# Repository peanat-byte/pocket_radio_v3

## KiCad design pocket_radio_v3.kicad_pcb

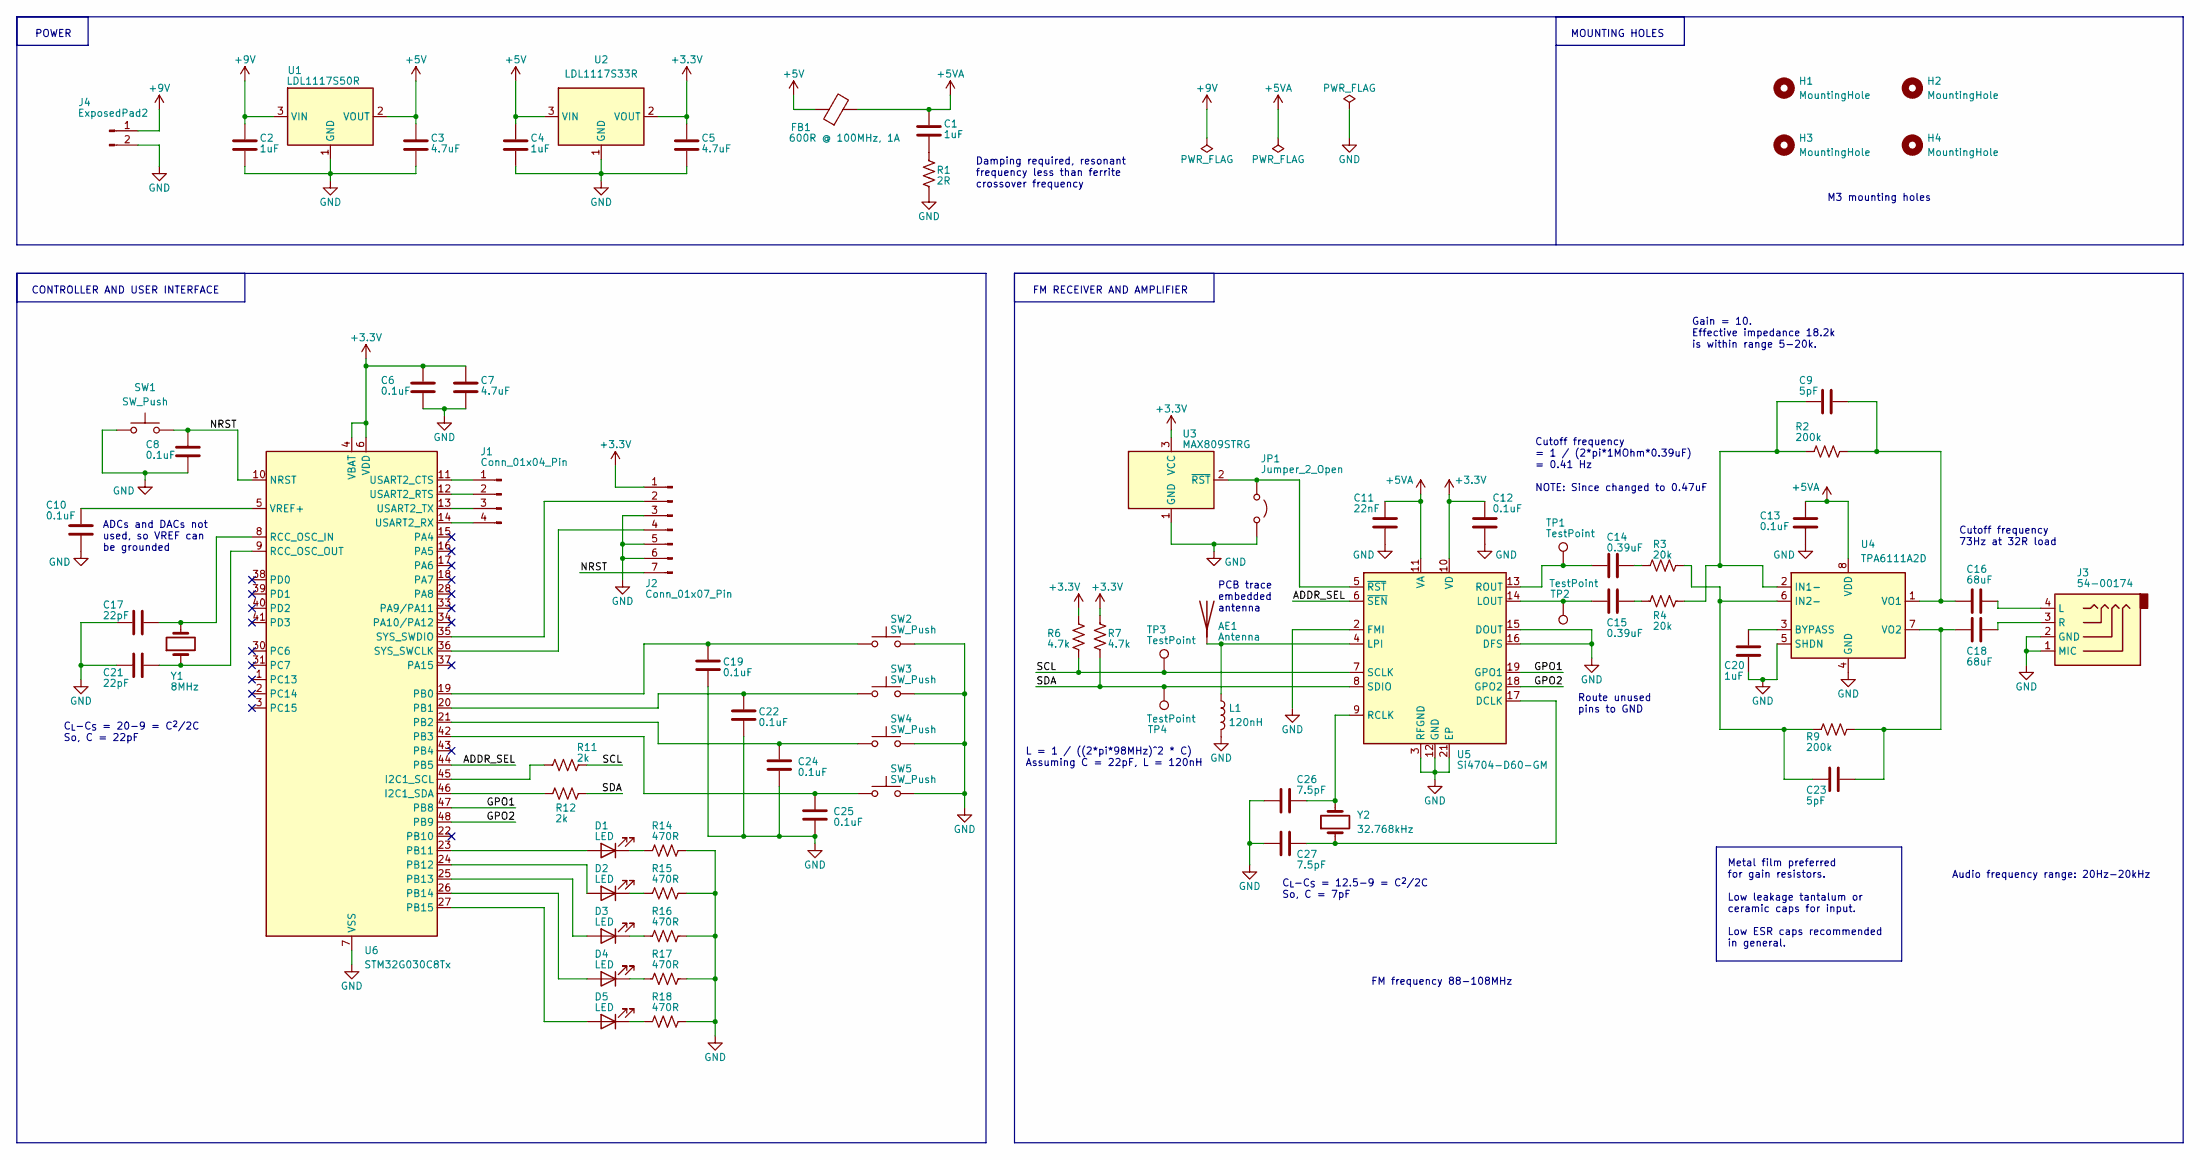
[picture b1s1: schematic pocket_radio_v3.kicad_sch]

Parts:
AE1: Antenna; EmbeddedAntenna_Si47xx
C1, C2, C4, C20: 1uF; C_0603_1608Metric
C3, C5, C7: 4.7uF; C_0603_1608Metric
C6, C8, C10, C12, C13, C19, C22, C24, C25: 0.1uF; C_0402_1005Metric
C9, C23: 5pF; C_0603_1608Metric
C11: 22nF; C_0402_1005Metric
C14, C15: 0.39uF; C_0603_1608Metric
C16, C18: 68uF; C_1210_3225Metric
C17, C21: 22pF; C_0402_1005Metric
C26, C27: 7.5pF; C_0402_1005Metric
D1, D2, D3, D4, D5: LED; D_0603_1608Metric
FB1: 600R @ 100MHz, 1A; L_0603_1608Metric
H1, H2, H3, H4: MountingHole; MountingHole_3.2mm_M3_ISO7380
J1: Conn_01x04_Pin; PinHeader_1x04_P2.54mm_Vertical_Tight
J2: Conn_01x07_Pin; PinHeader_1x07_P2.54mm_Vertical_Tight
J3: 54-00174; AudioJackConnector_4Conductor_3.5xL14mm_THT
J4: ExposedPad2; ExposedPad_2Conn_2x3mm_P3mm
JP1: Jumper_2_Open; ViaJumper_Pitch2.54mm_Drill0.7mm
L1: 120nH; L_0603_1608Metric
R1: 2R; R_0603_1608Metric
R2, R9: 200k; R_0805_2012Metric
R3, R4: 20k; R_0603_1608Metric
R6, R7: 4.7k; R_0603_1608Metric
R11, R12: 2k; R_0603_1608Metric
R14, R15, R16, R17, R18: 470R; R_0603_1608Metric
SW1, SW2, SW3, SW4, SW5: SW_Push; SW_SPST_PTS647_Sx38
TP1, TP2, TP3, TP4: TestPoint; TestPoint_Pad_D1.5mm
U1: LDL1117S50R; SOT-223-3_TabPin2
U2: LDL1117S33R; SOT-223-3_TabPin2
U3: MAX809STRG; SOT-23-3
U4: TPA6111A2D; SOIC-8_3.9x4.9mm_P1.27mm
U5: Si4704-D60-GM; Skyworks_Si470405-D60_QFN-20_1EP_3x3_P0.5mm
U6: STM32G030C8Tx; LQFP-48_7x7mm_P0.5mm
Y1: 8MHz; Crystal_SMD_2Pin_11.7x5mm
Y2: 32.768kHz; Crystal_SMD_3215-2Pin_3.2x1.5mm

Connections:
+3.3V: C5.1, C6.1, C7.1, C12.1, J2.1, R6.2, R7.2, U2.2 (VOUT), U3.3 (VCC), U5.10 (VD), U6.4 (VBAT), U6.6 (VDD)
+5V: C3.1, C4.1, FB1.1, U1.2 (VOUT), U2.3 (VIN)
+5VA: C1.1, C11.2, C13.1, FB1.2, U4.8 (VDD), U5.11 (VA)
+9V: C2.1, J4.1, U1.3 (VIN)
/ADDR_SEL: U5.6 (~SEN), U6.44 (PB5)
/GPO1: U5.19 (GPO1), U6.47 (PB8)
/GPO2: U5.18 (GPO2), U6.48 (PB9)
/NRST: C8.1, J2.7, SW1.2, U6.10 (NRST)
/SCL: R6.1, R11.1, TP3.1, U5.7 (SCLK)
/SDA: R7.1, R12.1, TP4.1, U5.8 (SDIO)
GND: C2.2, C3.2, C4.2, C5.2, C6.2, C7.2, C8.2, C10.2, C11.1, C12.2, C13.2, C17.1, C19.2, C20.2, C21.1, C22.2, C24.2, C25.2, C26.1, C27.1, J2.3, J2.5, J2.6, J3.1 (MIC), J3.2 (GND), J4.2, JP1.2 (B), L1.2, R1.1, R14.1, R15.1, R16.1, R17.1, R18.1, SW1.1, SW2.2, SW3.2, SW4.2, SW5.2, U1.1 (GND), U2.1 (GND), U3.1 (GND), U4.4 (GND), U4.5 (SHDN), U5.2 (FMI), U5.3 (RFGND), U5.12 (GND), U5.15 (DOUT), U5.16 (DFS), U5.21 (EP), U6.7 (VSS)
unnamed: AE1.1 (A), L1.1, U5.4 (LPI)
unnamed: C1.2, R1.2
unnamed: C14.1, R3.2
unnamed: C15.1, R4.2
unnamed: D1.2 (A), U6.23 (PB11)
unnamed: D1.1 (K), R14.2
unnamed: D2.2 (A), U6.24 (PB12)
unnamed: D2.1 (K), R15.2
unnamed: D3.2 (A), U6.25 (PB13)
unnamed: D3.1 (K), R16.2
unnamed: D4.2 (A), U6.26 (PB14)
unnamed: D4.1 (K), R17.2
unnamed: D5.2 (A), U6.27 (PB15)
unnamed: D5.1 (K), R18.2
unnamed: J1.1, U6.11 (USART2_CTS)
unnamed: J1.2, U6.12 (USART2_RTS)
unnamed: J1.3, U6.13 (USART2_TX)
unnamed: J1.4, U6.14 (USART2_RX)
unnamed: J2.2, U6.35 (SYS_SWDIO)
unnamed: J2.4, U6.36 (SYS_SWCLK)
unnamed: C16.1, J3.4 (L)
unnamed: C18.1, J3.3 (R)
unnamed: JP1.1 (A), U3.2 (~RST), U5.5 (~RST)
unnamed: C20.1, U4.3 (BYPASS)
unnamed: C9.2, R2.2, R4.1, U4.2 (IN1-)
unnamed: C23.2, R3.1, R9.2, U4.6 (IN2-)
unnamed: C9.1, C16.2, R2.1, U4.1 (VO1)
unnamed: C18.2, C23.1, R9.1, U4.7 (VO2)
unnamed: C27.2, U5.17 (DCLK), Y2.1
unnamed: C15.2, TP2.1, U5.14 (LOUT)
unnamed: C26.2, U5.9 (RCLK), Y2.2
unnamed: C14.2, TP1.1, U5.13 (ROUT)
unnamed: C19.1, SW2.1, U6.19 (PB0)
unnamed: C22.1, SW3.1, U6.20 (PB1)
unnamed: C24.1, SW4.1, U6.21 (PB2)
unnamed: C25.1, SW5.1, U6.42 (PB3)
unnamed: R11.2, U6.45 (I2C1_SCL)
unnamed: R12.2, U6.46 (I2C1_SDA)
unnamed: C17.2, U6.8 (RCC_OSC_IN), Y1.2
unnamed: C21.2, U6.9 (RCC_OSC_OUT), Y1.1
unnamed: C10.1, U6.5 (VREF+)

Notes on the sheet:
Audio frequency range: 20Hz-20kHz
Cutoff frequency 73Hz at 32R load
C_{L}-C_{S} = 20-9 = C^{2}/2C So, C = 22pF
L = 1 / ((2*pi*98MHz)^2 * C) Assuming C = 22pF, L = 120nH
Route unused pins to GND
Gain = 10. Effective impedance 18.2k is within range 5-20k.
FM frequency 88-108MHz
Metal film preferred for gain resistors. Low leakage tantalum or ceramic caps for input. Low ESR caps recommended in general.
FM RECEIVER AND AMPLIFIER
PCB trace embedded antenna
CONTROLLER AND USER INTERFACE
Damping required, resonant frequency less than ferrite crossover frequency
ADCs and DACs not used, so VREF can be grounded
M3 mounting holes
Cutoff frequency = 1 / (2*pi*1MOhm*0.39uF) = 0.41 Hz NOTE: Since changed to 0.47uF
C_{L}-C_{S} = 12.5-9 = C^{2}/2C So, C = 7pF
MOUNTING HOLES
POWER

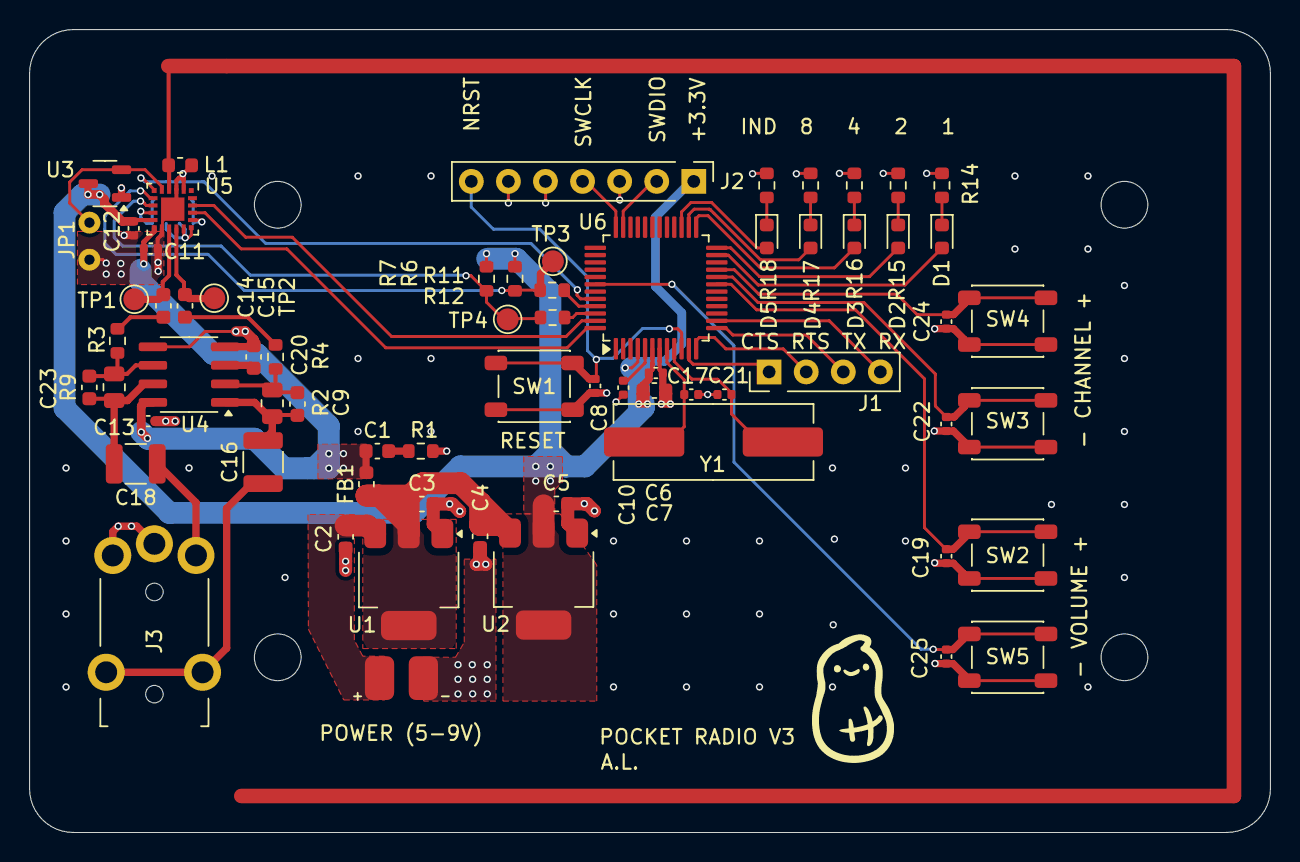
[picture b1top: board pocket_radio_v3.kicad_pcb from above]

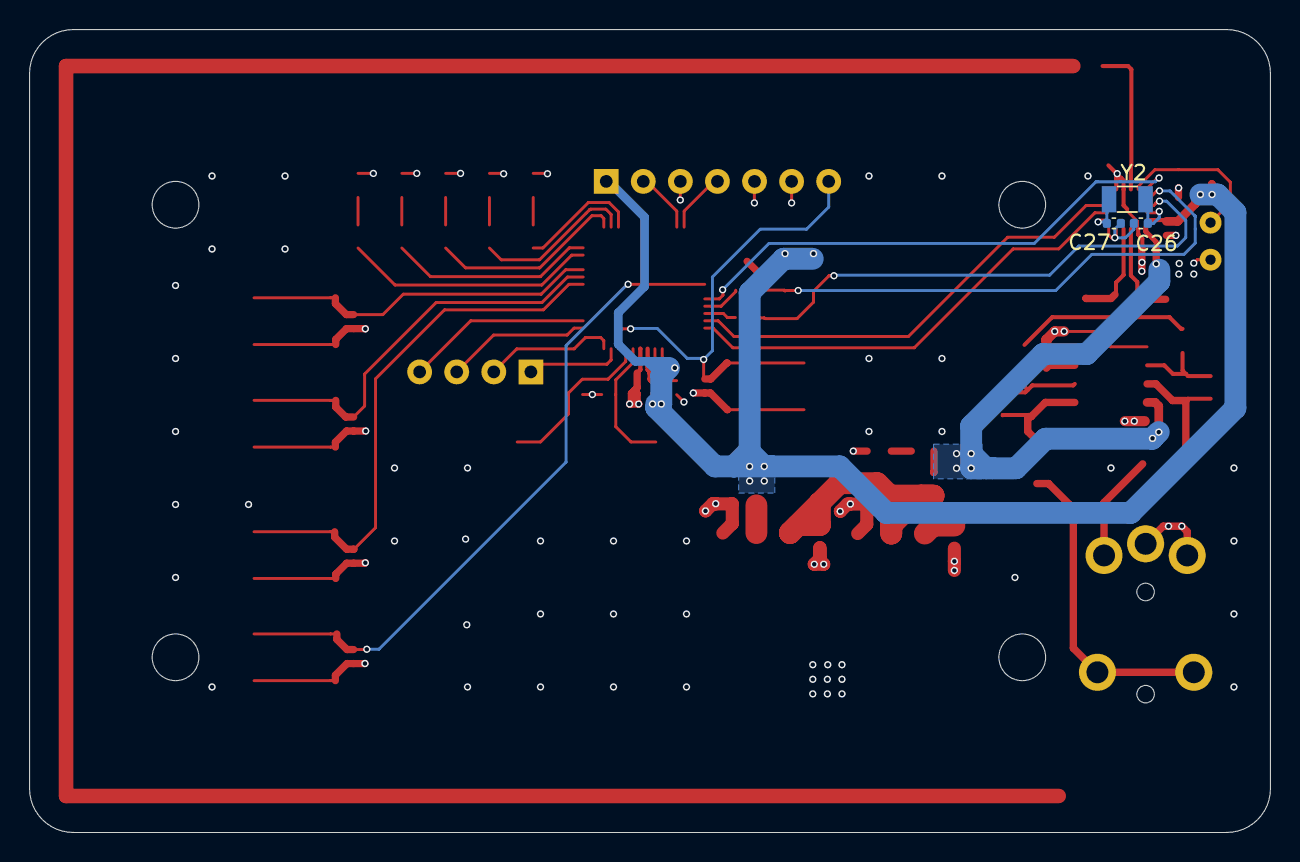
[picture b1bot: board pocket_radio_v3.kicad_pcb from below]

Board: 4 copper layers, 85.0 x 55.0 mm, 75 parts (3 on the bottom side), 52 nets.

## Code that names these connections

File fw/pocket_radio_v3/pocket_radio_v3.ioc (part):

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Mcu.Name=STM32G030C(6-8)Tx
Mcu.Package=LQFP48
Mcu.UserName=STM32G030C8Tx
PA0.Signal=USART2_CTS
PA1.Signal=USART2_RTS
PA13.Mode=Serial_Wire
PA13.Signal=SYS_SWDIO
PA14-BOOT0.Mode=Serial_Wire
PA14-BOOT0.Signal=SYS_SWCLK
PA2.Mode=Asynchronous
PA2.Signal=USART2_TX
PA3.Mode=Asynchronous
PA3.Signal=USART2_RX
PB0.GPIOParameters=GPIO_PuPd,GPIO_Label,GPIO_ModeDefaultEXTI
PB0.GPIO_Label=VOL_P
PB0.GPIO_ModeDefaultEXTI=GPIO_MODE_IT_FALLING
PB0.GPIO_PuPd=GPIO_PULLUP
PB0.Signal=GPXTI0
PB1.GPIOParameters=GPIO_PuPd,GPIO_Label,GPIO_ModeDefaultEXTI
PB1.GPIO_Label=CHAN_M
PB1.GPIO_ModeDefaultEXTI=GPIO_MODE_IT_FALLING
PB1.GPIO_PuPd=GPIO_PULLUP
PB1.Signal=GPXTI1
PB11.GPIOParameters=GPIO_Label
PB11.GPIO_Label=DIG1
PB11.Signal=GPIO_Output
PB12.GPIOParameters=GPIO_Label
PB12.GPIO_Label=DIG2
PB12.Signal=GPIO_Output
PB13.GPIOParameters=GPIO_Label
PB13.GPIO_Label=DIG4
PB13.Signal=GPIO_Output
PB14.GPIOParameters=GPIO_Label
PB14.GPIO_Label=DIG8
PB14.Signal=GPIO_Output
PB15.GPIOParameters=GPIO_Label
PB15.GPIO_Label=IND
PB15.Signal=GPIO_Output
PB2.GPIOParameters=GPIO_PuPd,GPIO_Label,GPIO_ModeDefaultEXTI
PB2.GPIO_Label=CHAN_P
PB2.GPIO_ModeDefaultEXTI=GPIO_MODE_IT_FALLING
PB2.GPIO_PuPd=GPIO_PULLUP
PB2.Signal=GPXTI2
PB3.GPIOParameters=GPIO_PuPd,GPIO_Label,GPIO_ModeDefaultEXTI
PB3.GPIO_Label=VOL_M
PB3.GPIO_ModeDefaultEXTI=GPIO_MODE_IT_FALLING
PB3.GPIO_PuPd=GPIO_PULLUP
PB3.Signal=GPXTI3
PB5.GPIOParameters=GPIO_PuPd,GPIO_Label
PB5.GPIO_Label=ADDR_SEL
PB5.GPIO_PuPd=GPIO_PULLDOWN
PB5.Signal=GPIO_Output
PB6.Mode=I2C
PB6.Signal=I2C1_SCL
PB7.Mode=I2C
PB7.Signal=I2C1_SDA
PB8.GPIOParameters=GPIO_Label
PB8.GPIO_Label=GPO1
PB8.Signal=GPIO_Input
PB9.GPIOParameters=GPIO_Label
PB9.GPIO_Label=GPO2
PB9.Signal=GPIO_Input
PF0-OSC_IN\ (PF0).Mode=HSE-External-Oscillator
PF0-OSC_IN\ (PF0).Signal=RCC_OSC_IN
PF1-OSC_OUT\ (PF1).Mode=HSE-External-Oscillator
PF1-OSC_OUT\ (PF1).Signal=RCC_OSC_OUT
RCC.HSE_VALUE=8000000
RCC.SYSCLKFreq_VALUE=48000000
RCC.SYSCLKSource=RCC_SYSCLKSOURCE_PLLCLK
board=custom

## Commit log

2025-07-28 Upload WIP
2025-07-31 Amost done schematic
2025-08-01 Schematic mostly done
2025-08-05 Start layout, add sim files
2025-08-07 Done layout, except for cosmetics and stitching vias
2025-08-08 Done and create fab files
2025-08-28 Start fw project
2025-09-02 Basic working code!
2025-09-03 Add seek function
2025-09-03 Add volume and channel button functionality
2025-09-07 GPO low, case stl file
